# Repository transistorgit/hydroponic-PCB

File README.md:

# hydroponic PCB

PCB schematics and layout for the hydroponic controller

For power supply, be carefull to choose a device that is powerful enough for the pump. If it's weak, the raspi will reset when the pump is switched on. I tried a 12V/2A successfully.

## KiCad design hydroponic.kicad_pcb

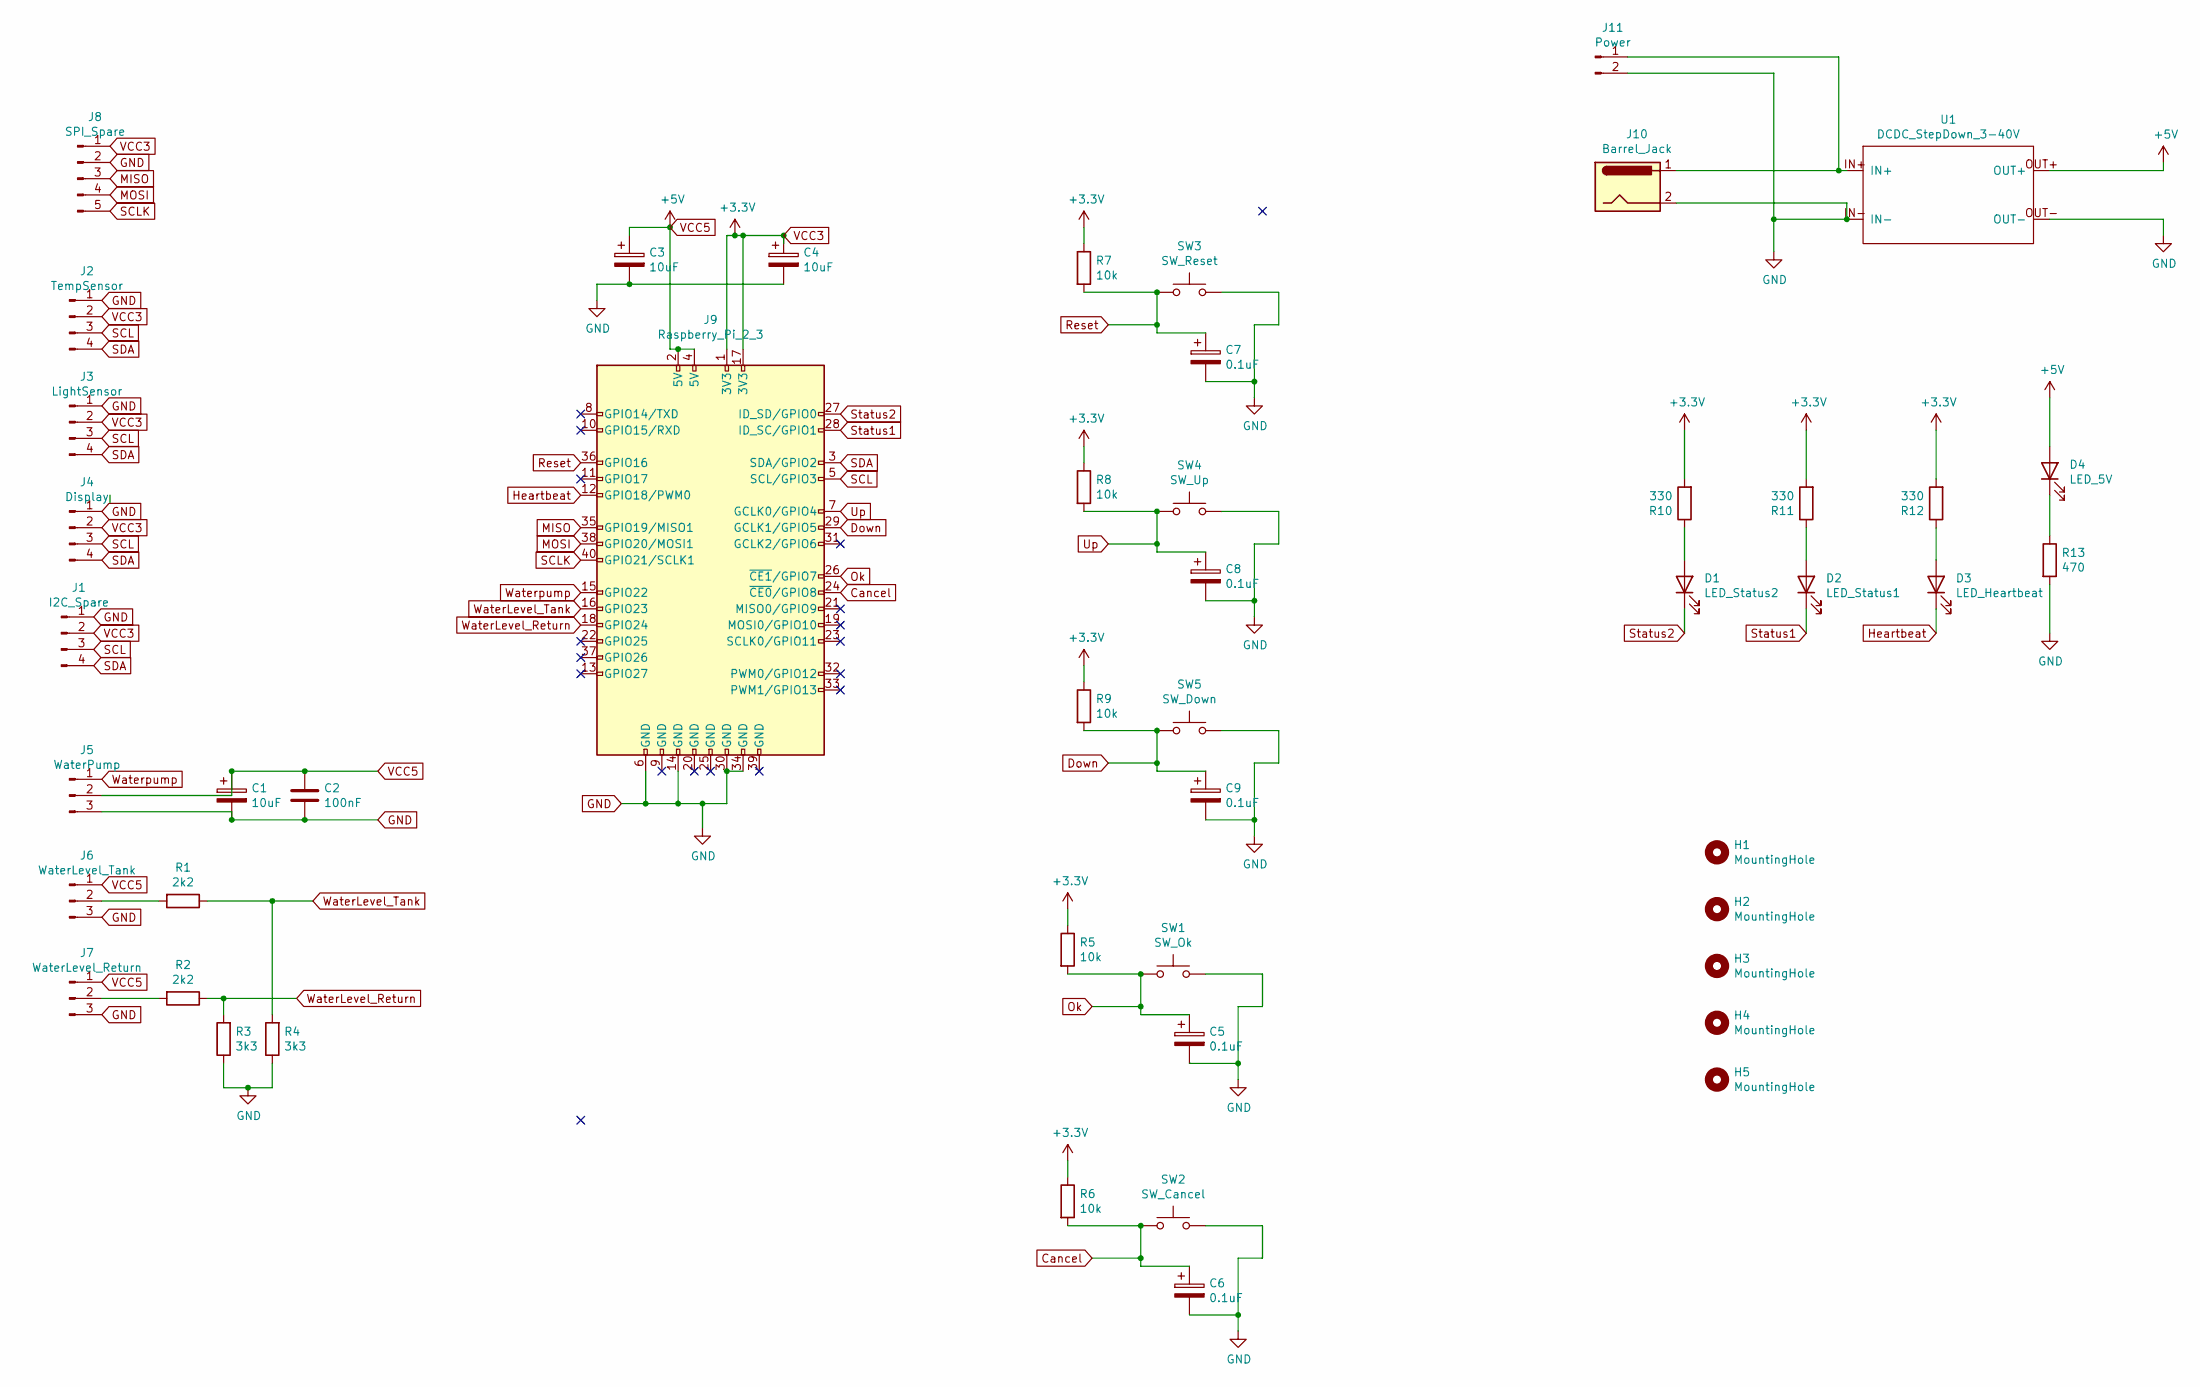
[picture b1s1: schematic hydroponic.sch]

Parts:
C1, C3, C4: 10uF; CP_Radial_D8.0mm_P5.00mm
C2: 100nF; C_Disc_D4.7mm_W2.5mm_P5.00mm
C5, C6, C7, C8, C9: 0.1uF; C_Disc_D4.7mm_W2.5mm_P5.00mm
D1: LED_Status2; LED_D5.0mm
D2: LED_Status1; LED_D5.0mm
D3: LED_Heartbeat; LED_D5.0mm
D4: LED_5V; LED_D5.0mm
H1, H2, H3, H4, H5: MountingHole; MountingHole_2.2mm_M2
J1: I2C_Spare; JST_XH_B4B-XH-A_1x04_P2.50mm_Vertical
J2: TempSensor; JST_XH_B4B-XH-A_1x04_P2.50mm_Vertical
J3: LightSensor; JST_XH_B4B-XH-A_1x04_P2.50mm_Vertical
J4: Display; JST_XH_B4B-XH-A_1x04_P2.50mm_Vertical
J5: WaterPump; JST_XH_B3B-XH-A_1x03_P2.50mm_Vertical
J6: WaterLevel_Tank; JST_XH_B3B-XH-A_1x03_P2.50mm_Vertical
J7: WaterLevel_Return; JST_XH_B3B-XH-A_1x03_P2.50mm_Vertical
J8: SPI_Spare; JST_XH_B5B-XH-A_1x05_P2.50mm_Vertical
J9: Raspberry_Pi_2_3; PinHeader_2x20_P2.54mm_Vertical
J10: Barrel_Jack; BarrelJack_Horizontal
J11: Power; JST_XH_B2B-XH-A_1x02_P2.50mm_Vertical
R1, R2: 2k2; R_Axial_DIN0207_L6.3mm_D2.5mm_P10.16mm_Horizontal
R3, R4: 3k3; R_Axial_DIN0207_L6.3mm_D2.5mm_P10.16mm_Horizontal
R5, R6, R7, R8, R9: 10k; R_Axial_DIN0207_L6.3mm_D2.5mm_P10.16mm_Horizontal
R10, R11, R12: 330; R_Axial_DIN0207_L6.3mm_D2.5mm_P10.16mm_Horizontal
R13: 470; R_Axial_DIN0207_L6.3mm_D2.5mm_P10.16mm_Horizontal
SW1: SW_Ok; SW_PUSH_6mm_H5mm
SW2: SW_Cancel; SW_PUSH_6mm_H5mm
SW3: SW_Reset; SW_PUSH_6mm_H5mm
SW4: SW_Up; SW_PUSH_6mm_H5mm
SW5: SW_Down; SW_PUSH_6mm_H5mm
U1: DCDC_StepDown_3-40V

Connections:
Cancel: C6.1, J9.24 (~CE0~/GPIO8), R6.2, SW2.1
Down: C9.1, J9.29 (GCLK1/GPIO5), R9.2, SW5.1
GND: C1.2, C2.2, C3.2, C4.2, C5.2, C6.2, C7.2, C8.2, C9.2, J1.1, J2.1, J3.1, J4.1, J5.3, J6.3, J7.3, J8.2, J9.6 (GND), J9.14 (GND), J9.30 (GND), J9.34 (GND), J10.2, J11.2, R3.1, R4.1, R13.2, SW1.2, SW2.2, SW3.2, SW4.2, SW5.2, U1.IN-, U1.OUT-
Heartbeat: D3.1 (K), J9.12 (GPIO18/PWM0)
MISO: J8.3, J9.35 (GPIO19/MISO1)
MOSI: J8.4, J9.38 (GPIO20/MOSI1)
unnamed: D1.2 (A), R10.1
unnamed: D2.2 (A), R11.1
unnamed: D3.2 (A), R12.1
unnamed: D4.1 (K), R13.1
unnamed: J6.2, R1.2
unnamed: J7.2, R2.2
unnamed: J10.1, J11.1, U1.IN+
Ok: C5.1, J9.26 (~CE1~/GPIO7), R5.2, SW1.1
Reset: C7.1, J9.36 (GPIO16), R7.2, SW3.1
SCL: J1.3, J2.3, J3.3, J4.3, J9.5 (SCL/GPIO3)
SCLK: J8.5, J9.40 (GPIO21/SCLK1)
SDA: J1.4, J2.4, J3.4, J4.4, J9.3 (SDA/GPIO2)
Status1: D2.1 (K), J9.28 (ID_SC/GPIO1)
Status2: D1.1 (K), J9.27 (ID_SD/GPIO0)
Up: C8.1, J9.7 (GCLK0/GPIO4), R8.2, SW4.1
VCC3: C4.1, J1.2, J2.2, J3.2, J4.2, J8.1, J9.1 (3V3), J9.17 (3V3), R5.1, R6.1, R7.1, R8.1, R9.1, R10.2, R11.2, R12.2
VCC5: C1.1, C2.1, C3.1, D4.2 (A), J5.2, J6.1, J7.1, J9.2 (5V), J9.4 (5V), U1.OUT+
WaterLevel_Return: J9.18 (GPIO24), R2.1, R3.2
WaterLevel_Tank: J9.16 (GPIO23), R1.1, R4.2
Waterpump: J5.1, J9.15 (GPIO22)

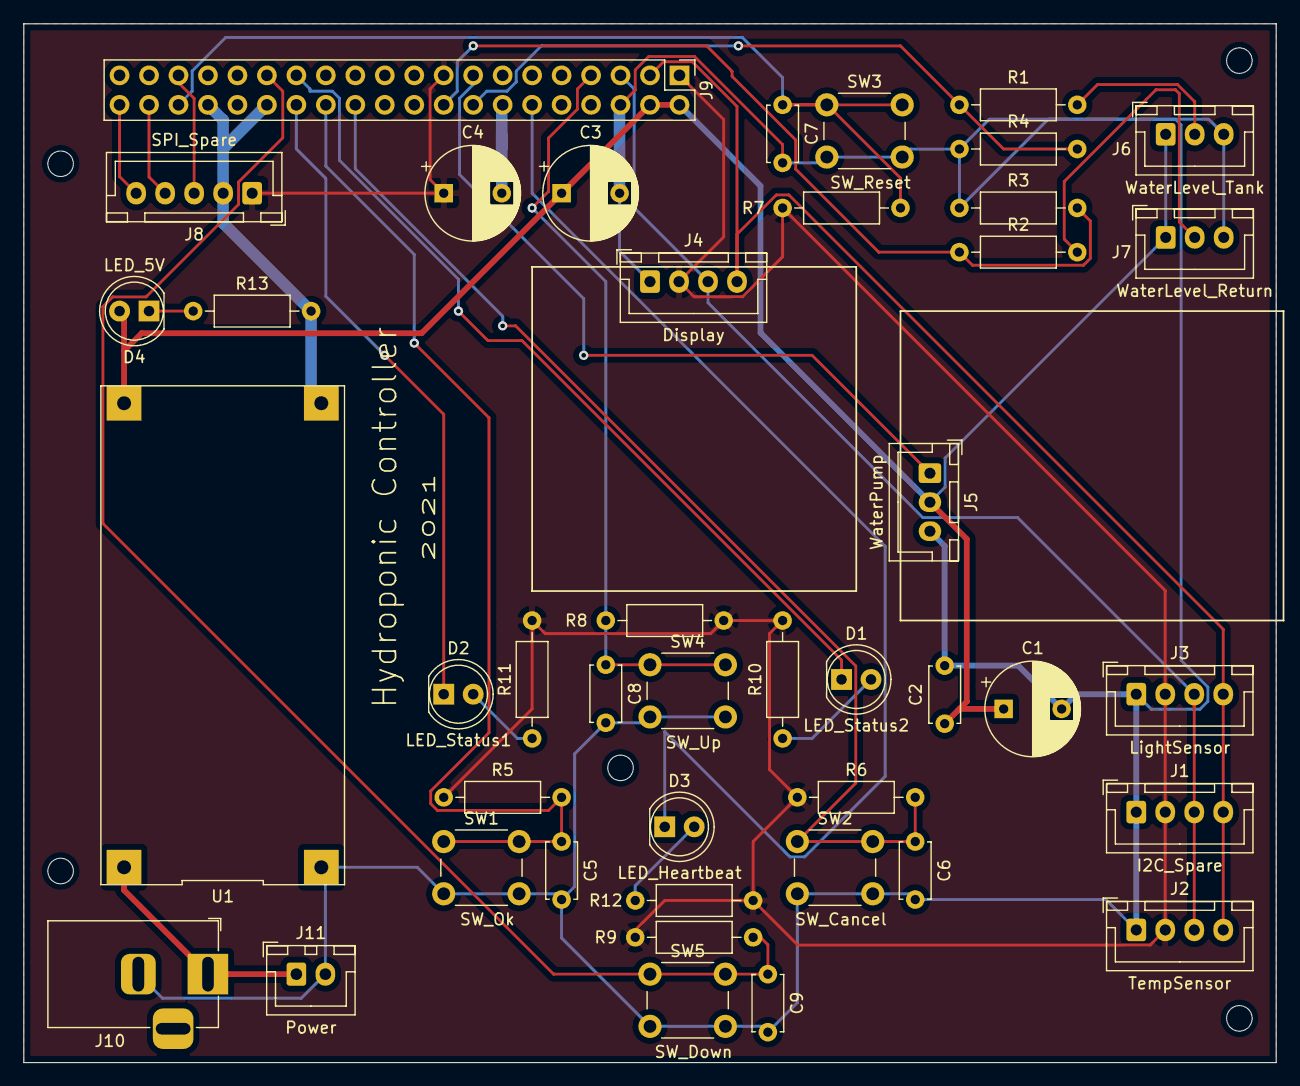
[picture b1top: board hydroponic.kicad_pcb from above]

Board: 2 copper layers, 108.0 x 89.5 mm, 48 parts (0 on the bottom side), 26 nets.

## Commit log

2023-04-22 initial
